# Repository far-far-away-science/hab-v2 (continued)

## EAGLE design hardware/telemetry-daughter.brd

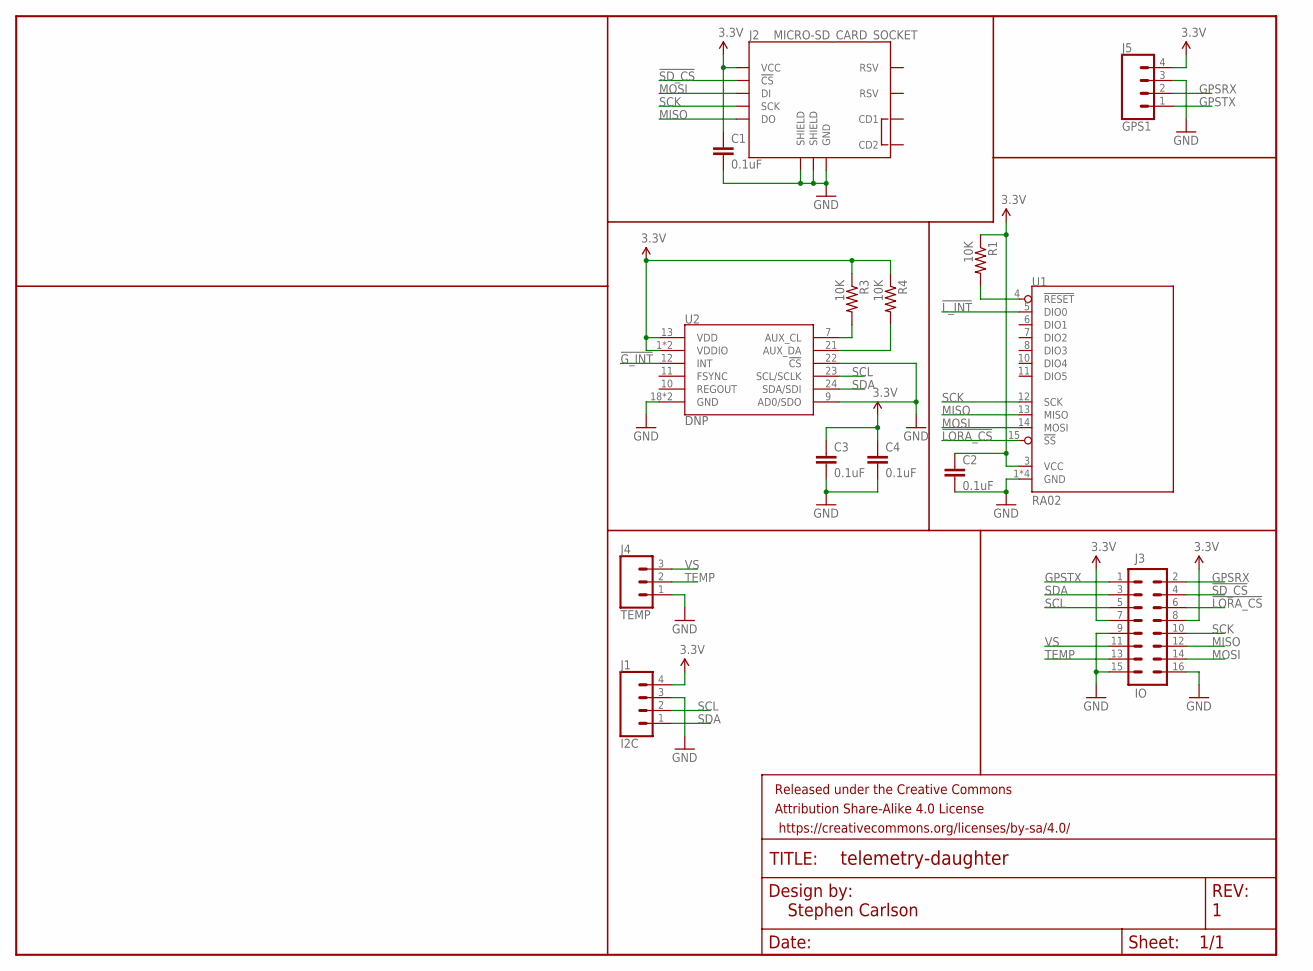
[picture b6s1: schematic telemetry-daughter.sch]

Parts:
C1, C2, C3, C4: 0.1uF; 0603
FRAME1: FRAME-LETTERNO_PACKAGE; DUMMY
J1: I2C; JST-4-PTH
J2: MICRO-SD_CARD_SOCKET; MICRO-SD-SOCKET
J3: IO; 2X8
J4: TEMP; JST-3-PTH
J5: GPS1; JST-4-PTH
R1, R3, R4: 10K; 0805
U1: RA02
U2: DNP; QFN24-3X3

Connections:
3.3V: C1.1, C2.1, C3.1, C4.1, J1.4, J2.VCC, J3.7, J3.8, J5.4, R1.1, R3.1, R4.1, U1.3 (VCC), U2.1 (VDDIO), U2.8 (VDDIO), U2.13 (VDD)
!G_INT!: U2.12 (INT)
!LORA_CS!: J3.6, U1.15 (!SS!)
!LORA_RST!: R1.2, U1.4 (!RESET!)
!L_INT!: U1.5 (DIO0)
!SD_CS!: J2.CS (!CS), J3.4
AUX_CL: R3.2, U2.7 (AUX_CL)
AUX_DA: R4.2, U2.21 (AUX_DA)
GND: C1.2, C2.2, C3.2, C4.2, J1.3, J2.GND, J2.GND1 (SHIELD), J2.GND3 (SHIELD), J3.9, J3.15, J3.16, J4.1, J5.3, U1.1 (GND), U1.2 (GND), U1.9 (GND), U1.16 (GND), U2.9 (AD0/SDO), U2.18 (GND), U2.20 (GND), U2.22 (!CS)
GPSRX: J3.2, J5.2
GPSTX: J3.1, J5.1
MISO: J2.DO, J3.12, U1.13 (MISO)
MOSI: J2.DI, J3.14, U1.14 (MOSI)
SCK: J2.SCLK (SCK), J3.10, U1.12 (SCK)
SCL: J1.2, J3.5, U2.23 (SCL/SCLK)
SDA: J1.1, J3.3, U2.24 (SDA/SDI)
TEMP: J3.13, J4.2
VS: J3.11, J4.3

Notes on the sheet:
Stephen Carlson

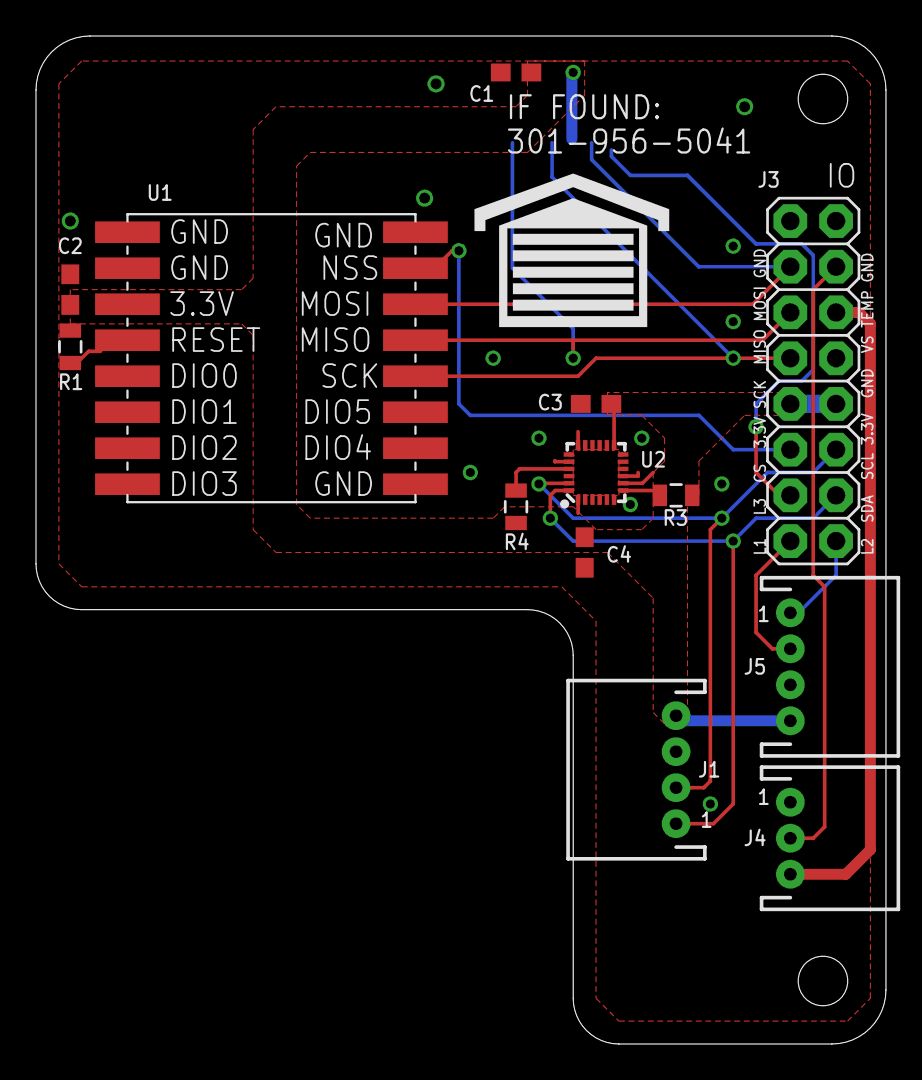
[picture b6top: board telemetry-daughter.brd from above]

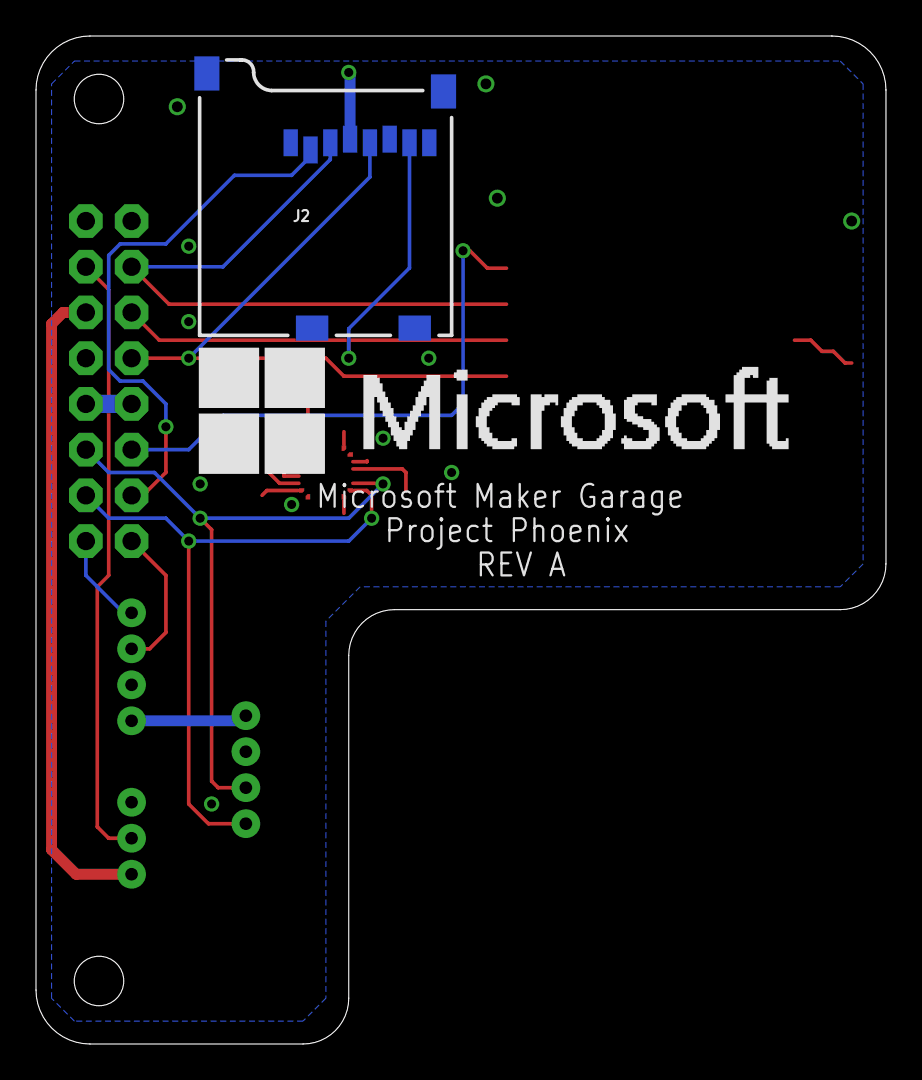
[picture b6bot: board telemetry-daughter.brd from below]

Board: 2 copper layers, 47.2 x 56.0 mm, 17 parts (2 on the bottom side), 16 nets.

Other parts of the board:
U$1: GARAGE
U$2: MSFT_LOGO

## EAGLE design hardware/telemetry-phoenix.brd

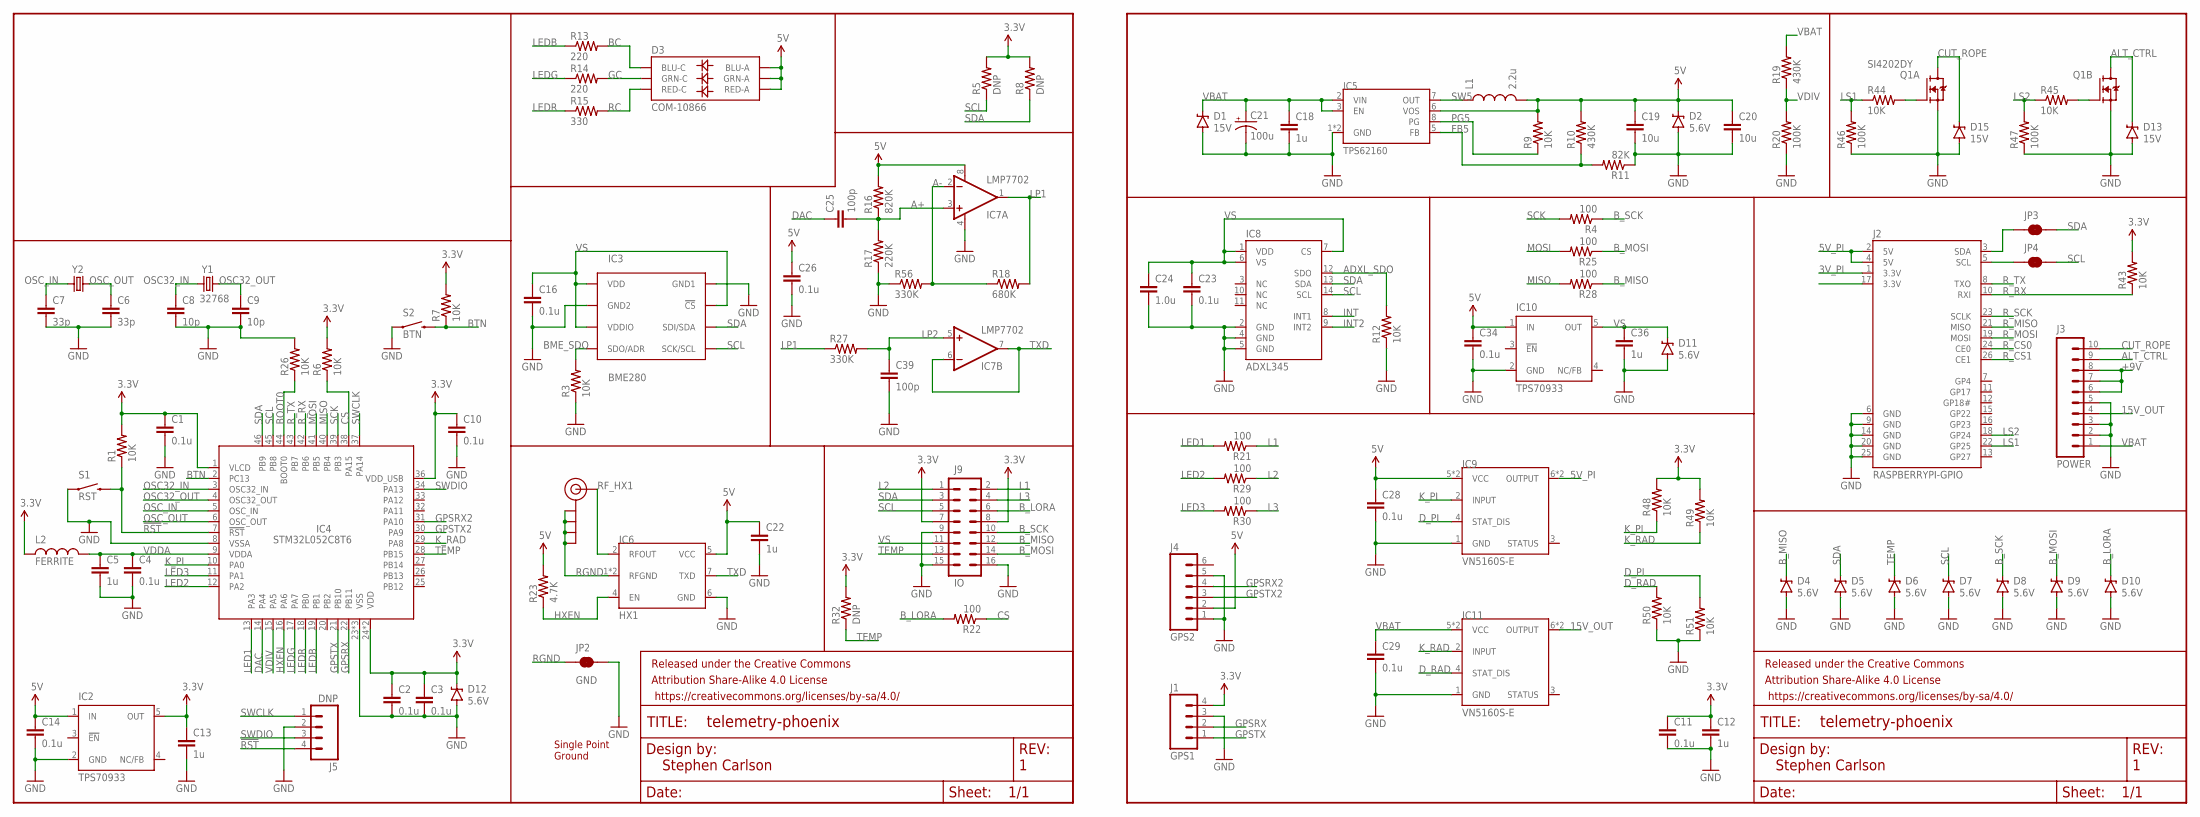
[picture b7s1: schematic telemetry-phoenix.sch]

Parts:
C1, C2, C3, C4, C10, C11, C14, C16, C23, C26, C28, C29, C34: 0.1u; 0805
C5, C12, C13, C18, C22, C36: 1u; 0805
C6, C7: 33p; 0805
C8, C9: 10p; 0805
C19, C20: 10u; 0805
C21: 100u; PANASONIC_E
C24: 1.0u; 0805
C25, C39: 100p; 0805
D1, D13, D15: 15V; SOD-323
D2, D4, D5, D6, D7, D8, D9, D10, D11, D12: 5.6V; SOD-323
D3: COM-10866; LED-TRICOLOR-5050
FRAME1, FRAME2: FRAME-LETTERNO_PACKAGE; DUMMY
IC2, IC10: TPS70933; SOT23-DBV
IC3: BME280; BME280_LGA
IC4: STM32L052C8T6; TQFP48
IC5: TPS62160; MSOP8
IC6: HX1
IC7: LMP7702; SO08
IC8: ADXL345; LGA14
IC9, IC11: VN5160S-E; SO8
J1: GPS1; 1X04
J2: RASPBERRYPI-GPIO; 2X13-PI
J3: POWER; 1X10_SCREW
J4: GPS2; 1X06-1MM
J5: DNP; 1X04_LOCK
J6: SMA_EDGE; SMA-EDGE
J9: IO; 2X8
JP2: GND; PAD-JUMPER-2-NC_BY_TRACE_YES_SILK
JP3: SDA; PAD-JUMPER-2-NC_BY_TRACE_YES_SILK
JP4: SCL; PAD-JUMPER-2-NC_BY_TRACE_YES_SILK
L1: 2.2u; 1008
L2: FERRITE; 1206
Q1: SI4202DY; SO8
R1, R3, R6, R7, R9, R12, R26, R43, R44, R45, R48, R49, R50, R51: 10K; 0805
R4, R21, R22, R25, R28, R29, R30: 100; 0805
R5, R8, R32: DNP; 0805
R10, R19: 430K; 0805
R11: 82K; 0805
R13, R14: 220; 0805
R15: 330; 0805
R16: 820K; 0805
R17: 220K; 0805
R18: 680K; 0805
R20, R46, R47: 100K; 0805
R23: 4.7K; 0805
R27, R56: 330K; 0805
S1: RST; TACTILE-PTH-THIN
S2: BTN; TACTILE-PTH-THIN
Y1: 32768; ABS25
Y2: 8M; CRYSTAL-TXC-7A

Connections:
3.3V: C1.1, C2.1, C3.1, C10.1, C11.1, C12.1, C13.1, D12.C, IC2.5 (OUT), IC4.1 (VLCD), IC4.24 (VDD), IC4.36 (VDD_USB), IC4.48 (VDD), J1.4, J9.7, J9.8, L2.1, R1.2, R5.2, R6.2, R7.2, R8.2, R32.2, R43.2, R48.2, R49.2
3V_PI: J2.1 (3.3V)
3V_PI2: J2.17 (3.3V)
5V: C14.1, C19.1, C20.1, C22.1, C26.1, C28.1, C34.1, D2.C, D3.1 (GRN-A), D3.2 (RED-A), D3.3 (BLU-A), IC2.1 (IN), IC5.6 (VOS), IC6.5 (VCC), IC7.8 (V+), IC9.5 (VCC), IC9.8 (VCC), IC10.1 (IN), J4.2, L1.2, R9.2, R10.2, R16.2, R23.2
5V_PI: IC9.6 (OUTPUT), IC9.7 (OUTPUT), J2.2 (5V), J2.4 (5V)
15V_OUT: IC11.6 (OUTPUT), IC11.7 (OUTPUT), J3.4
!RST!: IC4.7 (!RST!), J5.4, R1.1, S1.2
+9V: J3.6, J3.7, J3.8
A+: C25.2, IC7.3 (+IN), R16.1, R17.2
A-: IC7.2 (-IN), R18.1, R56.2
ACB: Q1.4 (G), R45.2
ADXL_SDO: IC8.12 (SDO), R12.2
ALT_CTRL: D13.C, J3.9, Q1.5 (D), Q1.6 (D)
BC: D3.4 (BLU-C), R13.2
BME_SDO: IC3.P$5 (SDO/ADR), R3.2
BOOT0: IC4.44 (BOOT0), R26.1
BTN: IC4.2 (PC13), R7.1, S2.2
B_LORA: D10.C, J9.6, R22.2
B_MISO: D4.C, J9.12, R28.1
B_MOSI: D9.C, J9.14, R25.1
B_SCK: D8.C, J9.10, R4.1
CRB: Q1.2 (G), R44.2
CS: IC4.38 (PA15), R6.1, R22.1
CUT_ROPE: D15.C, J3.10, Q1.7 (D), Q1.8 (D)
DAC: C25.1, IC4.14 (PA4)
D_PI: IC9.4 (STAT_DIS), R51.2
D_RAD: IC11.4 (STAT_DIS), R50.2
FB5: IC5.5 (FB), R10.1, R11.2
GC: D3.6 (GRN-C), R14.2
GND: C1.2, C2.2, C3.2, C4.2, C5.2, C6.2, C7.2, C8.2, C9.2, C10.2, C11.2, C12.2, C13.2, C14.2, C16.2, C18.2, C19.2, C20.2, C21.-, C22.2, C23.2, C24.2, C26.2, C28.2, C29.2, C34.2, C36.2, C39.2, D1.A, D2.A, D4.A, D5.A, D6.A, D7.A, D8.A, D9.A, D10.A, D11.A, D12.A, D13.A, D15.A, IC2.2 (GND), IC3.P$1 (GND1), IC3.P$7 (GND2), IC4.8 (VSSA), IC4.23 (VSS), IC4.35 (VSS), IC4.47 (VSS), IC5.1 (GND), IC5.4 (GND), IC6.6 (GND), IC7.4 (V-), IC8.2 (GND), IC8.4 (GND), IC8.5 (GND), IC9.1 (GND), IC10.2 (GND), IC11.1 (GND), J1.3, J2.6 (GND), J2.9 (GND), J2.14 (GND), J2.20 (GND), J2.25 (GND), J3.2, J3.3, J3.5, J4.1, J4.5, J5.2, J9.9, J9.15, J9.16, JP2.2, Q1.1 (S), Q1.3 (S), R3.1, R11.1, R12.1, R17.1, R20.1, R26.2, R46.1, R47.1, R50.1, R51.1, R56.1, S1.1, S2.1
GPSRX: IC4.22 (PB11), J1.2
GPSRX2: IC4.31 (PA10), J4.4
GPSTX: IC4.21 (PB10), J1.1
GPSTX2: IC4.30 (PA9), J4.3
HXEN: IC4.16 (PA6), IC6.4 (EN), R23.1
INT: IC8.8 (INT1)
INT2: IC8.9 (INT2)
K_PI: IC4.10 (PA0), IC9.2 (INPUT), R48.1
K_RAD: IC4.29 (PA8), IC11.2 (INPUT), R49.1
L1: J9.2, R21.1
L2: J9.1, R29.1
L3: J9.4, R30.1
LED1: IC4.13 (PA3), R21.2
LED2: IC4.12 (PA2), R29.2
LED3: IC4.11 (PA1), R30.2
LEDB: IC4.19 (PB1), R13.1
LEDG: IC4.17 (PA7), R14.1
LEDR: IC4.18 (PB0), R15.1
LP1: IC7.1 (OUT), R18.2, R27.1
LP2: C39.1, IC7.5 (+IN), R27.2
LS1: J2.22 (GP25), R44.1, R46.2
LS2: J2.18 (GP24), R45.1, R47.2
MISO: IC4.40 (PB4), R28.2
MOSI: IC4.41 (PB5), R25.2
OSC32_IN: C8.1, IC4.3 (OSC32_IN), Y1.1
OSC32_OUT: C9.1, IC4.4 (OSC32_OUT), Y1.4 (2)
OSC_IN: C7.1, IC4.5 (OSC_IN), Y2.P$1 (1)
OSC_OUT: C6.1, IC4.6 (OSC_OUT), Y2.P$2 (2)
PG5: IC5.8 (PG), R9.1
RC: D3.5 (RED-C), R15.2
RF_HX1: IC6.2 (RFOUT), J6.SIG (SIGNAL)
RGND: IC6.1 (RFGND), IC6.3 (RFGND), J6.GND@0 (GND), J6.GND@1 (GND), J6.GND@2 (GND), J6.GND@3 (GND), JP2.1
R_CS0: J2.24 (CE0)
R_CS1: J2.26 (CE1)
R_MISO: J2.21 (MISO)
R_MOSI: J2.19 (MOSI)
R_RX: IC4.42 (PB6), J2.10 (RXI), R43.1
R_SCK: J2.23 (SCLK)
R_SCL: J2.5 (SCL), JP4.1
R_SDA: J2.3 (SDA), JP3.1
R_TX: IC4.43 (PB7), J2.8 (TXO)
SCK: IC4.39 (PB3), R4.2
SCL: D7.C, IC3.P$4 (SCK/SCL), IC4.45 (PB8), IC8.14 (SCL), J9.5, JP4.2, R5.1
SDA: D5.C, IC3.P$3 (SDI/SDA), IC4.46 (PB9), IC8.13 (SDA), J9.3, JP3.2, R8.1
SW5: IC5.7 (OUT), L1.1
SWCLK: IC4.37 (PA14), J5.1
SWDIO: IC4.34 (PA13), J5.3
TEMP: D6.C, IC4.28 (PB15), J9.13, R32.1
TXD: IC6.7 (TXD), IC7.6 (-IN), IC7.7 (OUT)
VBAT: C18.1, C21.+, C29.1, D1.C, IC5.2 (VIN), IC5.3 (EN), IC11.5 (VCC), IC11.8 (VCC), J3.1, R19.2
VDDA: C4.1, C5.1, IC4.9 (VDDA), L2.2
VDIV: IC4.15 (PA5), R19.1, R20.2
VS: C16.1, C23.1, C24.1, C36.1, D11.C, IC3.P$2 (!CS), IC3.P$6 (VDDIO), IC3.P$8 (VDD), IC8.1 (VDD), IC8.6 (VS), IC8.7 (CS), IC10.5 (OUT), J9.11

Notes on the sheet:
Stephen Carlson
Single Point Ground

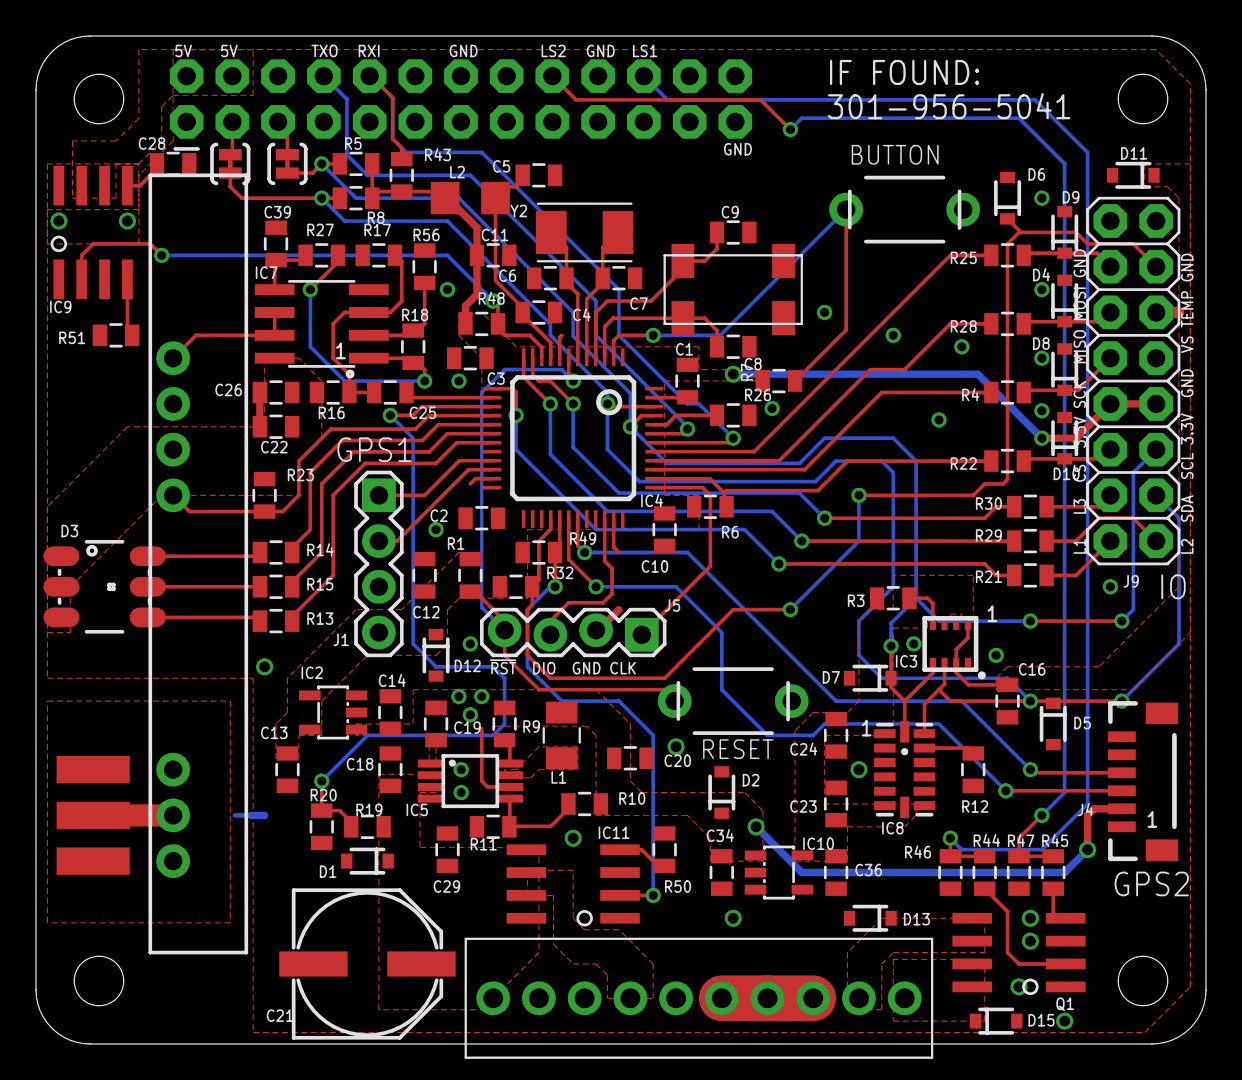
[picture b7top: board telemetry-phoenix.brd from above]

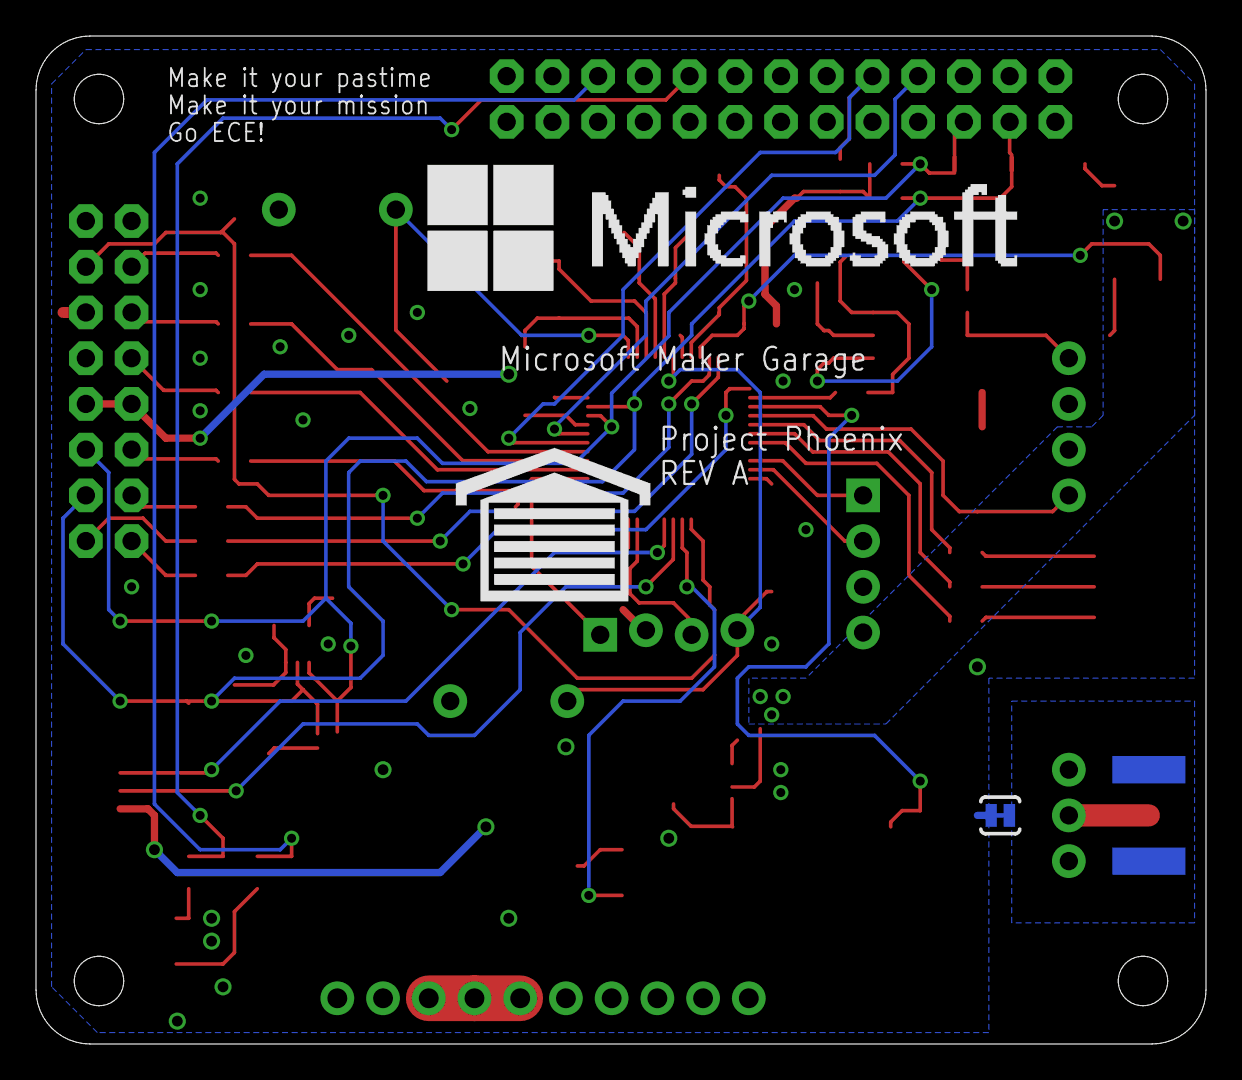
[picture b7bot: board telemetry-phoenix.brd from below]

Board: 2 copper layers, 65.0 x 56.0 mm, 113 parts (3 on the bottom side), 74 nets.

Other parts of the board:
U$1: GARAGE
U$2: MSFT_LOGO

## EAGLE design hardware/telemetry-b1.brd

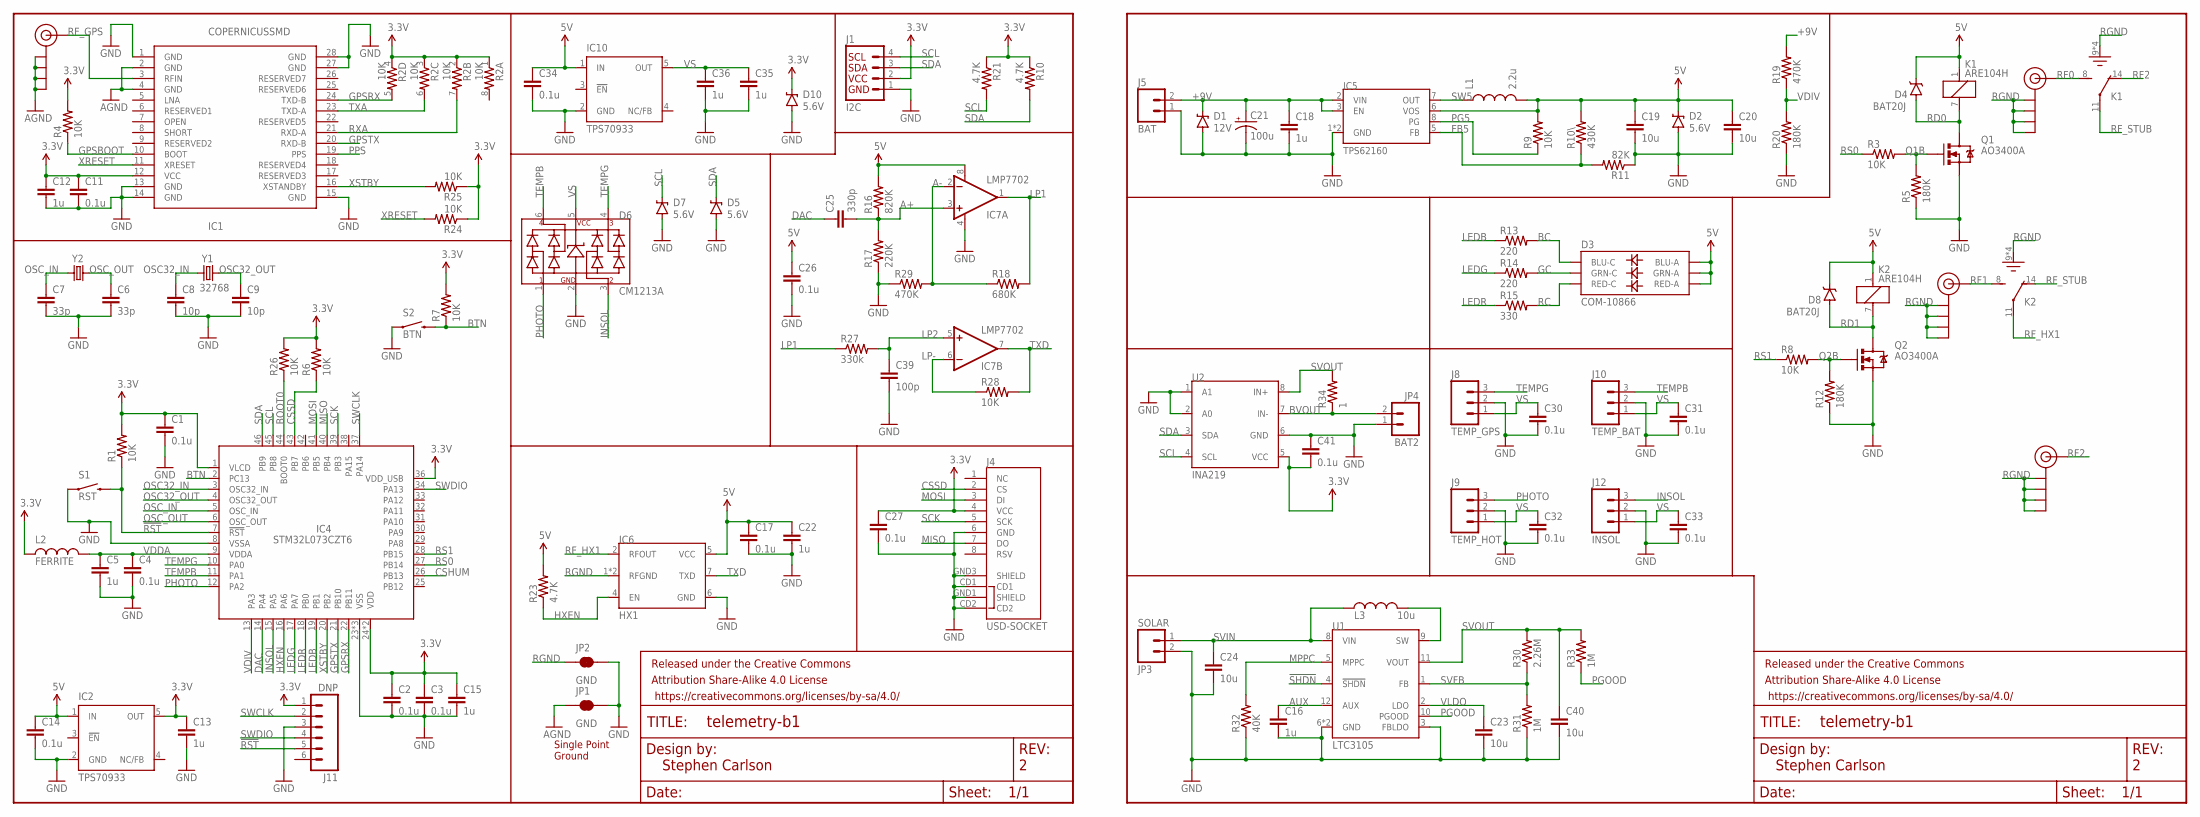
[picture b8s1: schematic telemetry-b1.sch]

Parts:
C1, C2, C3, C4, C11, C14, C17, C26, C27, C30, C31, C32, C33, C34, C41: 0.1u; 0805
C5, C12, C13, C15, C16, C18, C22, C35, C36: 1u; 0805
C6, C7: 33p; 0805
C8, C9: 10p; 0805
C19, C20, C23, C24, C40: 10u; 0805
C21: 100u; CPOL-RADIAL-10UF-25V
C25: 330p; 0805
C39: 100p; 0805
D1: 12V; SOD-323
D2, D5, D7, D10: 5.6V; SOD-323
D3: COM-10866; LED-TRICOLOR-5050
D4, D8: BAT20J; SOD-323
D6: CM1213A; SC70-6L
FRAME1, FRAME2: FRAME-LETTERNO_PACKAGE; DUMMY
IC1: COPERNICUSSMD; COPERNICUS
IC2, IC10: TPS70933; SOT23-DBV
IC4: STM32L073CZT6; TQFP48
IC5: TPS62160; MSOP8
IC6: HX1
IC7: LMP7702; SO08
J1: I2C; 1X04_NO_SILK
J3, J6, J7, J13: SMA_EDGE; SMA-EDGE
J4: USD-SOCKET; MICROSD_1:1
J5: BAT; 1X02
J8: TEMP_GPS; JST-3-PTH
J9: TEMP_HOT; JST-3-PTH
J10: TEMP_BAT; JST-3-PTH
J11: DNP; 1X06_LOCK
J12: INSOL; JST-3-PTH
JP1, JP2: GND; PAD-JUMPER-2-NC_BY_TRACE_YES_SILK
JP3: SOLAR; 1X02
JP4: BAT2; 1X02
K1, K2: ARE104H; RFDIL14
L1: 2.2u; 1008
L2: FERRITE; 1206
L3: 10u; SRN6045
Q1, Q2: AO3400A; SOT23-3
R1, R3, R4, R6, R7, R8, R9, R24, R25, R26, R28: 10K; 0805
R2: 10K; 0603-ARV
R5, R12, R20: 180K; 0805
R10, R21, R23: 4.7K; 0805
R10\: 430K; 0805
R11: 82K; 0805
R13, R14: 220; 0805
R15: 330; 0805
R16: 820K; 0805
R17: 220K; 0805
R18: 680K; 0805
R19, R29: 470K; 0805
R27: 330k; 0805
R30: 2.26M; 0805
R31, R33: 1M; 0805
R32: 40K; 0805
R34: 1; 0805
S1: RST; TACTILE-PTH-THIN
S2: BTN; TACTILE-PTH-THIN
U1: LTC3105; MSOP12
U2: INA219; SO8
Y1: 32768; ABS25
Y2: 8M; HC49UP

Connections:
3.3V: C1.1, C2.1, C3.1, C11.1, C12.1, C13.1, C15.1, C27.1, C41.2, D10.C, IC1.12 (VCC), IC2.5 (OUT), IC4.1 (VLCD), IC4.24 (VDD), IC4.36 (VDD_USB), IC4.48 (VDD), J1.2, J4.4 (VCC), J11.1, L2.1, R1.2, R2.1, R2.2 (1), R2.3 (1), R2.4 (1), R4.2, R6.2, R7.2, R10.1, R21.1, R24.1, R25.1, R26.2, U2.5 (VCC)
5V: C14.1, C17.1, C19.1, C20.1, C22.1, C26.1, C34.1, D2.C, D3.1 (GRN-A), D3.2 (RED-A), D3.3 (BLU-A), D4.C, D8.C, IC2.1 (IN), IC5.6 (VOS), IC6.5 (VCC), IC7.8 (V+), IC10.1 (IN), K1.1, K2.1, L1.2, R9.2, R10\.2, R16.2, R23.2
!RST!: IC4.7 (!RST!), J11.5, R1.1, S1.2
!SHDN!: U1.4 (!SHDN!)
+9V: C18.1, C21.1 (+), D1.C, IC5.2 (VIN), IC5.3 (EN), J5.2, R19.2
A+: C25.2, IC7.3 (+IN), R16.1, R17.2
A-: IC7.2 (-IN), R18.1, R29.2
AGND: IC1.2 (GND), IC1.4 (GND), J7.GND@0 (GND), J7.GND@1 (GND), J7.GND@2 (GND), J7.GND@3 (GND), JP1.1
AUX: C16.1, U1.12 (AUX)
BC: D3.4 (BLU-C), R13.2
BOOT0: IC4.44 (BOOT0), R26.1
BTN: IC4.2 (PC13), R7.1, S2.2
BVOUT: JP4.2, R34.1, U2.7 (IN-)
CSHUM: IC4.26 (PB13)
CSSD: IC4.43 (PB7), J4.2 (CS), R6.1
DAC: C25.1, IC4.14 (PA4)
FB5: IC5.5 (FB), R10\.1, R11.2
GC: D3.6 (GRN-C), R14.2
GND: C1.2, C2.2, C3.2, C4.2, C5.2, C6.2, C7.2, C8.2, C9.2, C11.2, C12.2, C13.2, C14.2, C15.2, C16.2, C17.2, C18.2, C19.2, C20.2, C21.2 (-), C22.2, C23.2, C24.2, C26.2, C27.2, C30.2, C31.2, C32.2, C33.2, C34.2, C35.2, C36.2, C39.2, C40.2, C41.1, D1.A, D2.A, D5.A, D6.2 (GND), D7.A, D10.A, IC1.1 (GND), IC1.13 (GND), IC1.14 (GND), IC1.15 (GND), IC1.27 (GND), IC1.28 (GND), IC2.2 (GND), IC4.8 (VSSA), IC4.23 (VSS), IC4.35 (VSS), IC4.47 (VSS), IC5.1 (GND), IC5.4 (GND), IC6.6 (GND), IC7.4 (V-), IC10.2 (GND), J1.1, J4.6 (GND), J4.CD1, J4.CD2, J4.GND1 (SHIELD), J4.GND3 (SHIELD), J5.1, J8.2, J9.2, J10.2, J11.3, J12.2, JP1.2, JP2.2, JP3.2, JP4.1, Q1.2 (S), Q2.2 (S), R5.1, R11.1, R12.1, R17.1, R20.1, R29.1, R31.1, R32.1, S1.1, S2.1, U1.3 (FBLDO), U1.6 (GND), U1.7 (GND), U2.1 (A1), U2.2 (A0), U2.6 (GND)
GPSBOOT: IC1.10 (BOOT), R4.1
GPSRX: IC1.24 (TXD-B), IC4.22 (PB11), R2.5 (2)
GPSTX: IC1.20 (RXD-B), IC4.21 (PB10)
HXEN: IC4.16 (PA6), IC6.4 (EN), R23.1
INSOL: D6.3 (CH2), IC4.15 (PA5), J12.3
LEDB: IC4.19 (PB1), R13.1
LEDG: IC4.17 (PA7), R14.1
LEDR: IC4.18 (PB0), R15.1
LP1: IC7.1 (OUT), R18.2, R27.1
LP2: C39.1, IC7.5 (+IN), R27.2
LP-: IC7.6 (-IN), R28.1
MISO: IC4.40 (PB4), J4.7 (DO)
MOSI: IC4.41 (PB5), J4.3 (DI)
MPPC: R32.2, U1.5 (MPPC)
OSC32_IN: C8.1, IC4.3 (OSC32_IN), Y1.1
OSC32_OUT: C9.1, IC4.4 (OSC32_OUT), Y1.4 (2)
OSC_IN: C7.1, IC4.5 (OSC_IN), Y2.1
OSC_OUT: C6.1, IC4.6 (OSC_OUT), Y2.2
PG5: IC5.8 (PG), R9.1
PGOOD: R33.1, U1.10 (PGOOD)
PHOTO: D6.1 (CH1), IC4.12 (PA2), J9.3
PPS: IC1.19 (PPS)
Q1B: Q1.1 (G), R3.2, R5.2
Q2B: Q2.1 (G), R8.2, R12.2
RC: D3.5 (RED-C), R15.2
RD0: D4.A, K1.7 (2), Q1.3 (D)
RD1: D8.A, K2.7 (2), Q2.3 (D)
RF0: J6.SIG (SIGNAL), K1.8 (S)
RF1: J3.SIG (SIGNAL), K2.8 (S)
RF2: J13.SIG (SIGNAL), K1.14 (O)
RF_GPS: IC1.3 (RFIN), J7.SIG (SIGNAL)
RF_HX1: IC6.2 (RFOUT), K2.11
RF_STUB: K1.11, K2.14 (O)
RGND: IC6.1 (RFGND), IC6.3 (RFGND), J3.GND@0 (GND), J3.GND@1 (GND), J3.GND@2 (GND), J3.GND@3 (GND), J6.GND@0 (GND), J6.GND@1 (GND), J6.GND@2 (GND), J6.GND@3 (GND), J13.GND@0 (GND), J13.GND@1 (GND), J13.GND@2 (GND), J13.GND@3 (GND), JP2.1, K1.9 (GND), K1.10 (GND), K1.12 (GND), K1.13 (GND), K2.9 (GND), K2.10 (GND), K2.12 (GND), K2.13 (GND)
RS0: IC4.27 (PB14), R3.1
RS1: IC4.28 (PB15), R8.1
RXA: IC1.21 (RXD-A), R2.7 (2)
SCK: IC4.39 (PB3), J4.5 (SCK)
SCL: D7.C, IC4.45 (PB8), J1.4, R21.2, U2.4 (SCL)
SDA: D5.C, IC4.46 (PB9), J1.3, R10.2, U2.3 (SDA)
SVFB: R30.1, R31.2, U1.1 (FB)
SVIN: C24.1, JP3.1, L3.1, U1.8 (VIN)
SVOUT: C40.1, R30.2, R33.2, R34.2, U1.11 (VOUT), U2.8 (IN+)
SW: L3.2, U1.9 (SW)
SW5: IC5.7 (OUT), L1.1
SWCLK: IC4.37 (PA14), J11.2
SWDIO: IC4.34 (PA13), J11.4
TEMPB: D6.6 (CH4), IC4.11 (PA1), J10.3
TEMPG: D6.4 (CH3), IC4.10 (PA0), J8.3
TXA: IC1.23 (TXD-A), R2.6 (2)
TXD: IC6.7 (TXD), IC7.7 (OUT), R28.2
VDDA: C4.1, C5.1, IC4.9 (VDDA), L2.2
VDIV: IC4.13 (PA3), R19.1, R20.2
VLDO: C23.1, U1.2 (LDO)
VS: C30.1, C31.1, C32.1, C33.1, C35.1, C36.1, D6.5 (VCC), IC10.5 (OUT), J8.1, J9.1, J10.1, J12.1
XRESET: IC1.11 (XRESET), R24.2
XSTBY: IC1.16 (XSTANDBY), IC4.20 (PB2), R25.2

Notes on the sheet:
Stephen Carlson
Single Point Ground

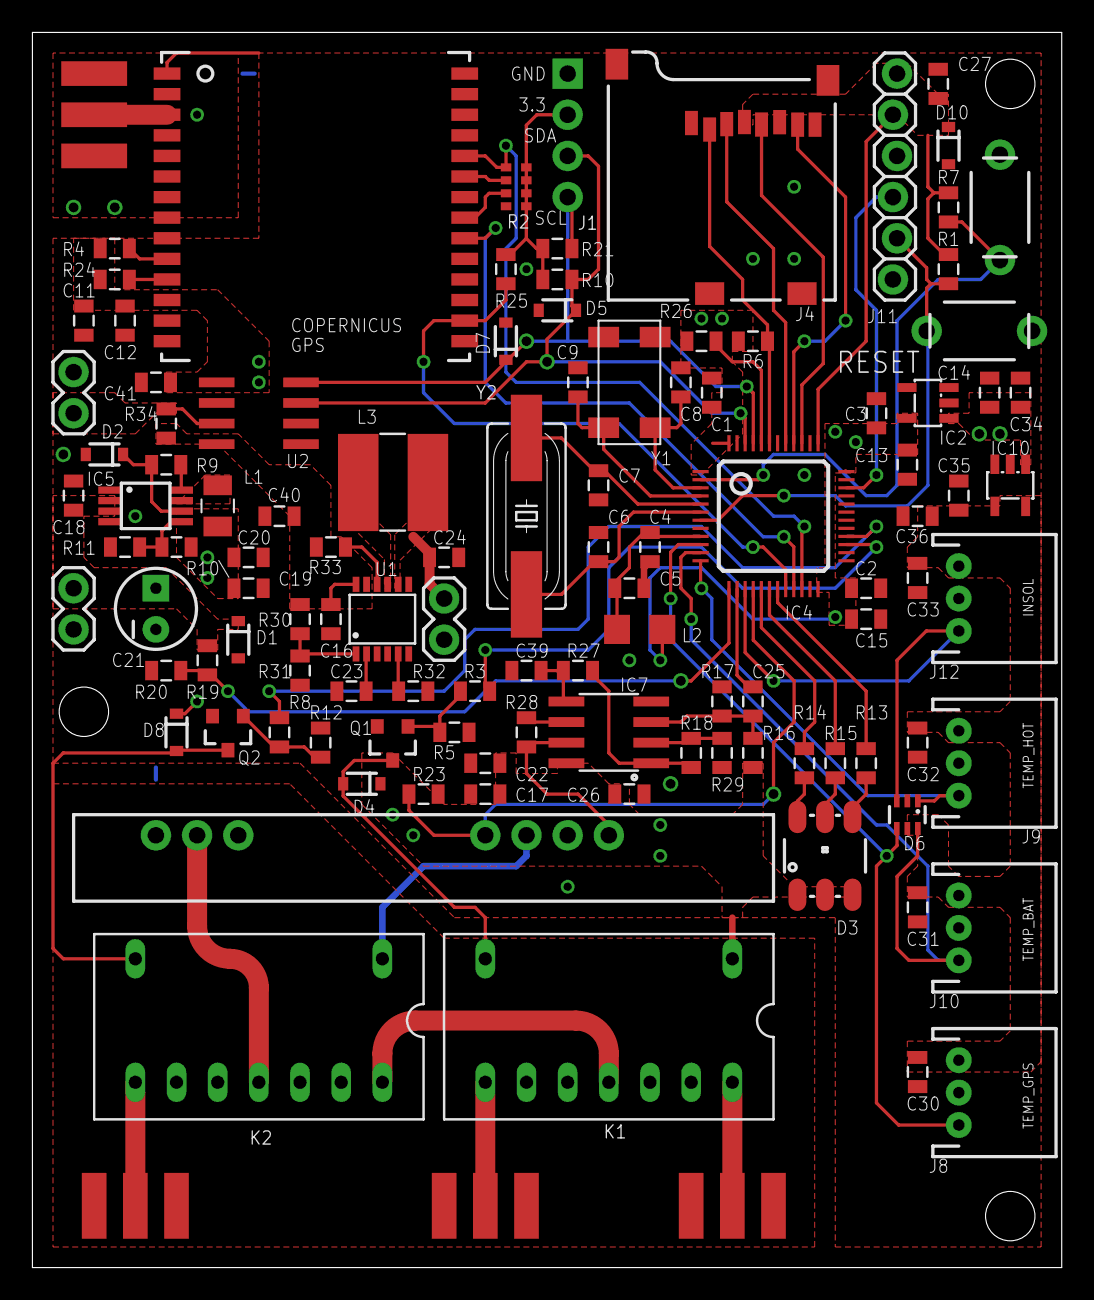
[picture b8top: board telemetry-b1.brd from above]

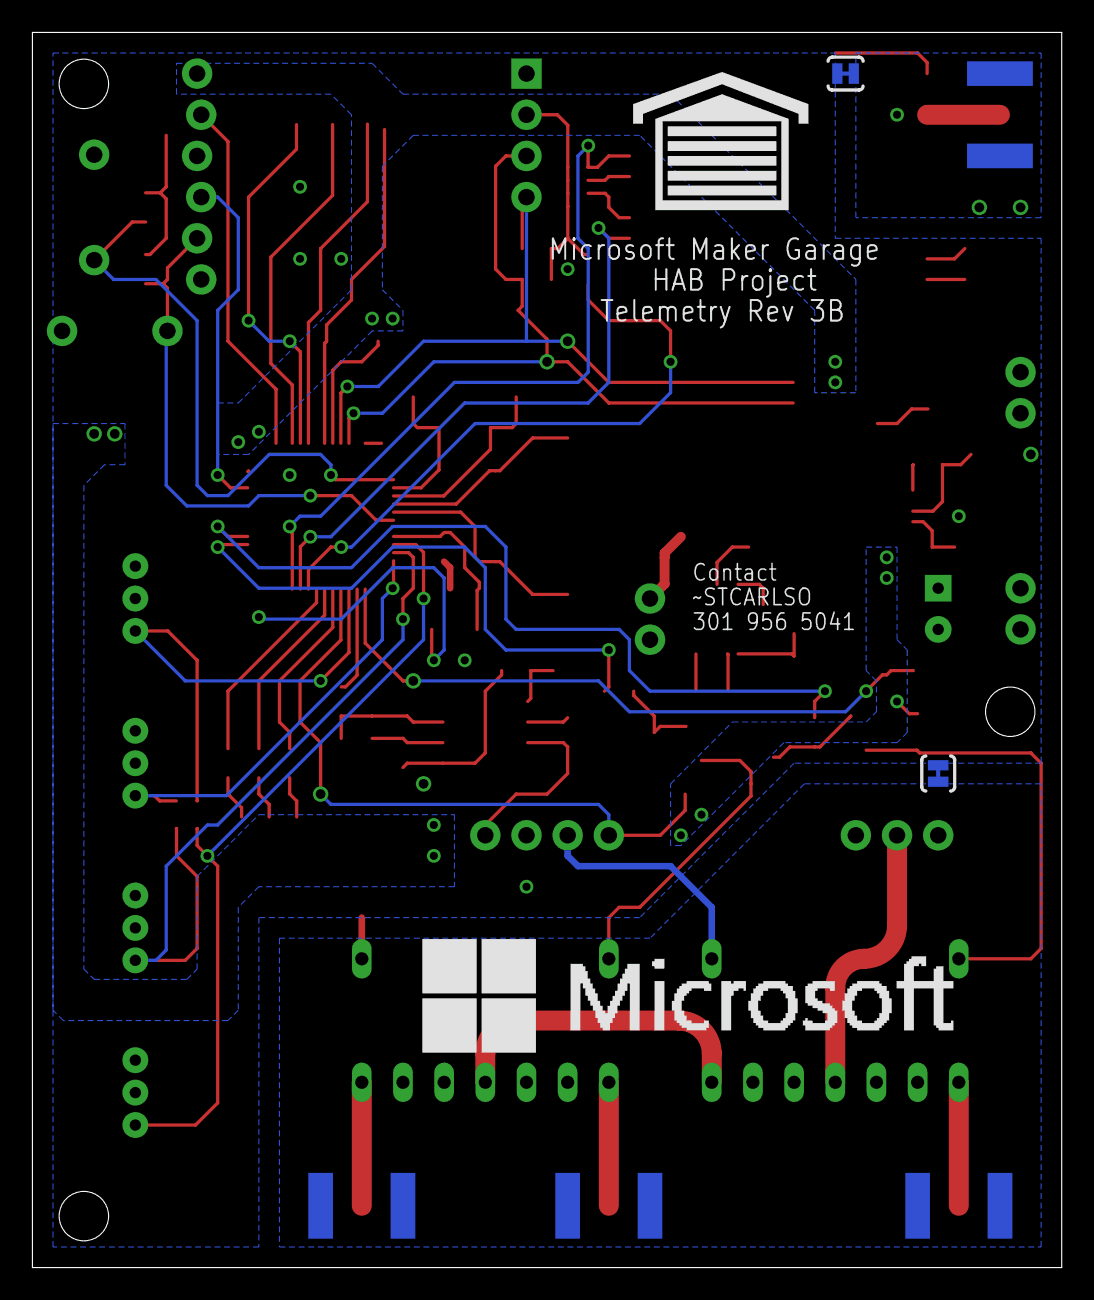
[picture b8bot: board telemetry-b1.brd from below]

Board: 2 copper layers, 63.5 x 76.2 mm, 119 parts (4 on the bottom side), 73 nets.

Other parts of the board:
U$2: GARAGE
U$5: MSFT_LOGO
